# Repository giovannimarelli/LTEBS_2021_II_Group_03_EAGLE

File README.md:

# LTEBS_2021_II_Group_03_EAGLE
Laboratorio di Tecnologie Elettroniche e Biosensori S2021-II Group 03 EAGLE

In the Library folder, inside the Group_03_Library file we have inserted the two additional devices we were required to make and the microcontroller, for which we modified the footprint (setting line width of the silkscreen according to the manufacturer's specs); other devices referred to Sparkfun Library were not included, supposing to be in your possess. 
For what regards the TMUX device, we built the UQFN package, as specified by the description table inside the PDF, even if inside the provided schematic pins followed the 
TSSOP pattern. The same applies for the CY8CKIT059-TARGET: the table said to pick this, whereas inside the schematic the one used was the CY8CKIT059-TARGET_3: as before, we 
followed the table specs.

Inside the .brd file, Power Jack device looks like it exits the pcb: we intentionally placed it there folowing some examples online. 

All traces are of 10 mils, as you asked in the assignment document. However, due to the small dimension of the MUX, the design rules generated errors due to the clearance of the traces connecting the pads to the other pins. To overcome this problem, we decided to convert the width of all the traces connected to the MUX to 8 mils.

We added Silkscreen references for all SMD components, respecting manufacturer's rules of clearance and distance from the pads (8 mil from any exposed copper part).

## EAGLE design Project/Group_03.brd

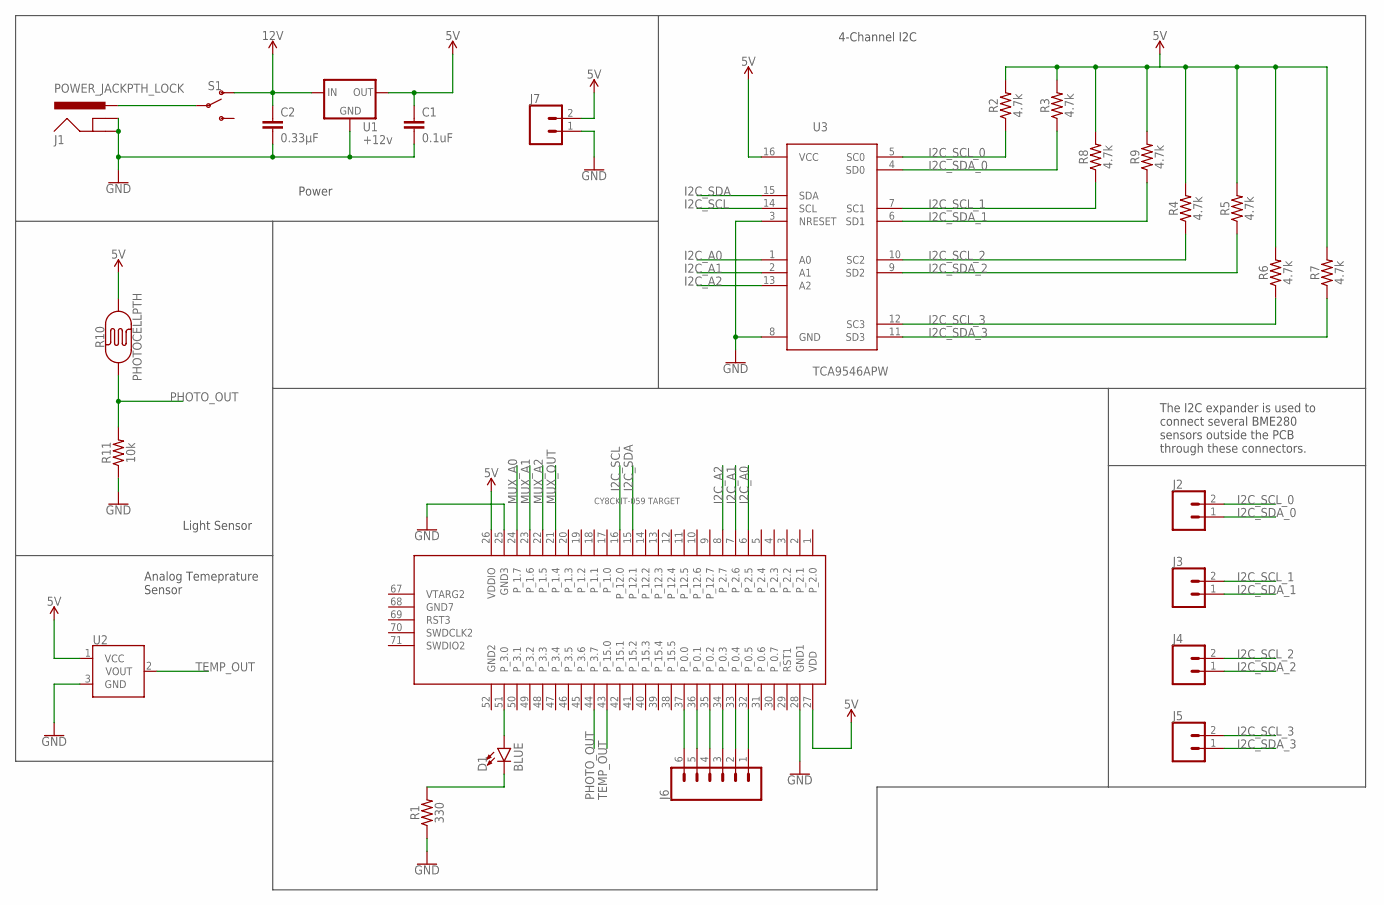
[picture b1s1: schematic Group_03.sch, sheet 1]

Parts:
C1: 0.1uF; CAP-PTH-SMALL-KIT
C2: 0.33µF; 0805
D1: BLUE; LED-1206
J1: POWER_JACKPTH_LOCK; POWER_JACK_PTH_LOCK
J2, J3, J4, J5, J7: CONN_02; 1X02
J6: CONN_06LOCK; 1X06_LOCK
R1: 330; AXIAL-0.3
R2, R3, R4, R5, R6, R7, R8, R9: 4.7k; 0603
R10: PHOTOCELLPTH; PHOTOCELL
R11: 10k; 0603
S1: SWITCH-SPDT-PTH-11.6X4.0MM; SWITCH_SPDT_PTH_11.6X4.0MM
U1: +12v; TO-252
U2: TMP36GT9; TO-92
U3: TCA9546APW; TSSOP16
U$1: CY8CKIT-059_TARGET

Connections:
5V: C1.1, J7.2, R2.2, R3.2, R4.2, R5.2, R6.2, R7.2, R8.2, R9.2, R10.2, U1.2 (OUT), U2.1 (VCC), U3.16 (VCC), U$1.26 (VDDIO), U$1.27 (VDD); also elsewhere on the board
12V: C2.1, S1.1 (O), U1.1 (IN)
GND: C1.2, C2.2, J1.GND, J1.GNDBREAK, J7.1, R1.P$1 (1), R11.1, U1.3 (GND), U2.3 (GND), U3.3 (NRESET), U3.8 (GND), U$1.25 (GND3), U$1.28 (GND1); also elsewhere on the board
I2C_A0: U3.1 (A0), U$1.6 (P_2.5)
I2C_A1: U3.2 (A1), U$1.7 (P_2.6)
I2C_A2: U3.13 (A2), U$1.8 (P_2.7)
I2C_SCL: U3.14 (SCL), U$1.16 (P_12.0)
I2C_SCL_0: J2.2, R2.1, U3.5 (SC0)
I2C_SCL_1: J3.2, R8.1, U3.7 (SC1)
I2C_SCL_2: J4.2, R4.1, U3.10 (SC2)
I2C_SCL_3: J5.2, R6.1, U3.12 (SC3)
I2C_SDA: U3.15 (SDA), U$1.15 (P_12.1)
I2C_SDA_0: J2.1, R3.1, U3.4 (SD0)
I2C_SDA_1: J3.1, R9.1, U3.6 (SD1)
I2C_SDA_2: J4.1, R5.1, U3.9 (SD2)
I2C_SDA_3: J5.1, R7.1, U3.11 (SD3)
MUX_A0: U$1.24 (P_1.7); also elsewhere on the board
MUX_A1: U$1.23 (P_1.6); also elsewhere on the board
MUX_A2: U$1.22 (P_1.5); also elsewhere on the board
MUX_OUT: U$1.21 (P_1.4); also elsewhere on the board
unnamed: J1.PWR, S1.2
unnamed: J6.1, U$1.32 (P_0.5)
unnamed: J6.2, U$1.33 (P_0.4)
unnamed: J6.3, U$1.34 (P_0.3)
unnamed: J6.4, U$1.35 (P_0.2)
unnamed: J6.5, U$1.36 (P_0.1)
unnamed: J6.6, U$1.37 (P_0.0)
unnamed: D1.A, U$1.51 (P_3.0)
unnamed: D1.C, R1.P$2 (2)
PHOTO_OUT: R10.1, R11.2, U$1.44 (P_3.7)
TEMP_OUT: U2.2 (VOUT), U$1.43 (P_15.0)

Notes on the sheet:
The I2C expander is used to connect several BME280 sensors outside the PCB through these connectors.
Analog Temeprature Sensor
Light Sensor
Power
4-Channel I2C

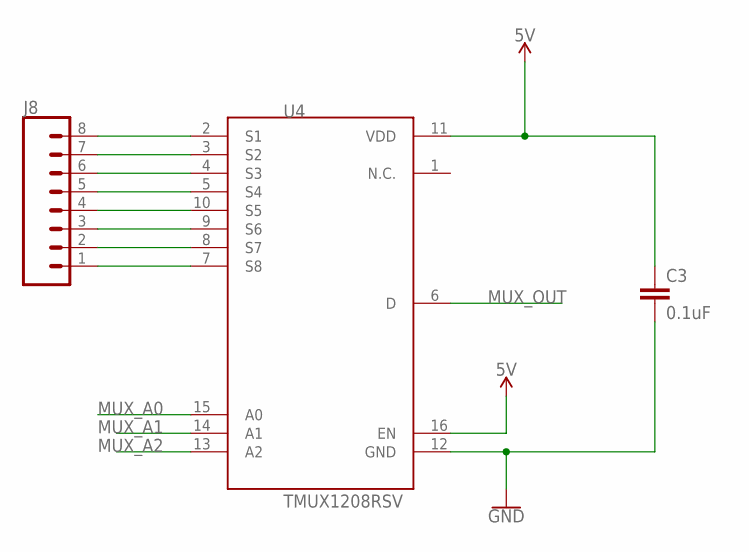
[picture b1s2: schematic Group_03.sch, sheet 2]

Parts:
C3: 0.1uF; CAP-PTH-SMALL-KIT
J8: CONN_08LOCK; 1X08_LOCK
U4: TMUX1208RSV; QFN16

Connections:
5V: C3.1, U4.11 (VDD), U4.16 (EN); also elsewhere on the board
GND: C3.2, U4.12 (GND); also elsewhere on the board
MUX_A0: U4.15 (A0); also elsewhere on the board
MUX_A1: U4.14 (A1); also elsewhere on the board
MUX_A2: U4.13 (A2); also elsewhere on the board
MUX_OUT: U4.6 (D); also elsewhere on the board
unnamed: J8.8, U4.2 (S1)
unnamed: J8.7, U4.3 (S2)
unnamed: J8.6, U4.4 (S3)
unnamed: J8.5, U4.5 (S4)
unnamed: J8.4, U4.10 (S5)
unnamed: J8.3, U4.9 (S6)
unnamed: J8.2, U4.8 (S7)
unnamed: J8.1, U4.7 (S8)

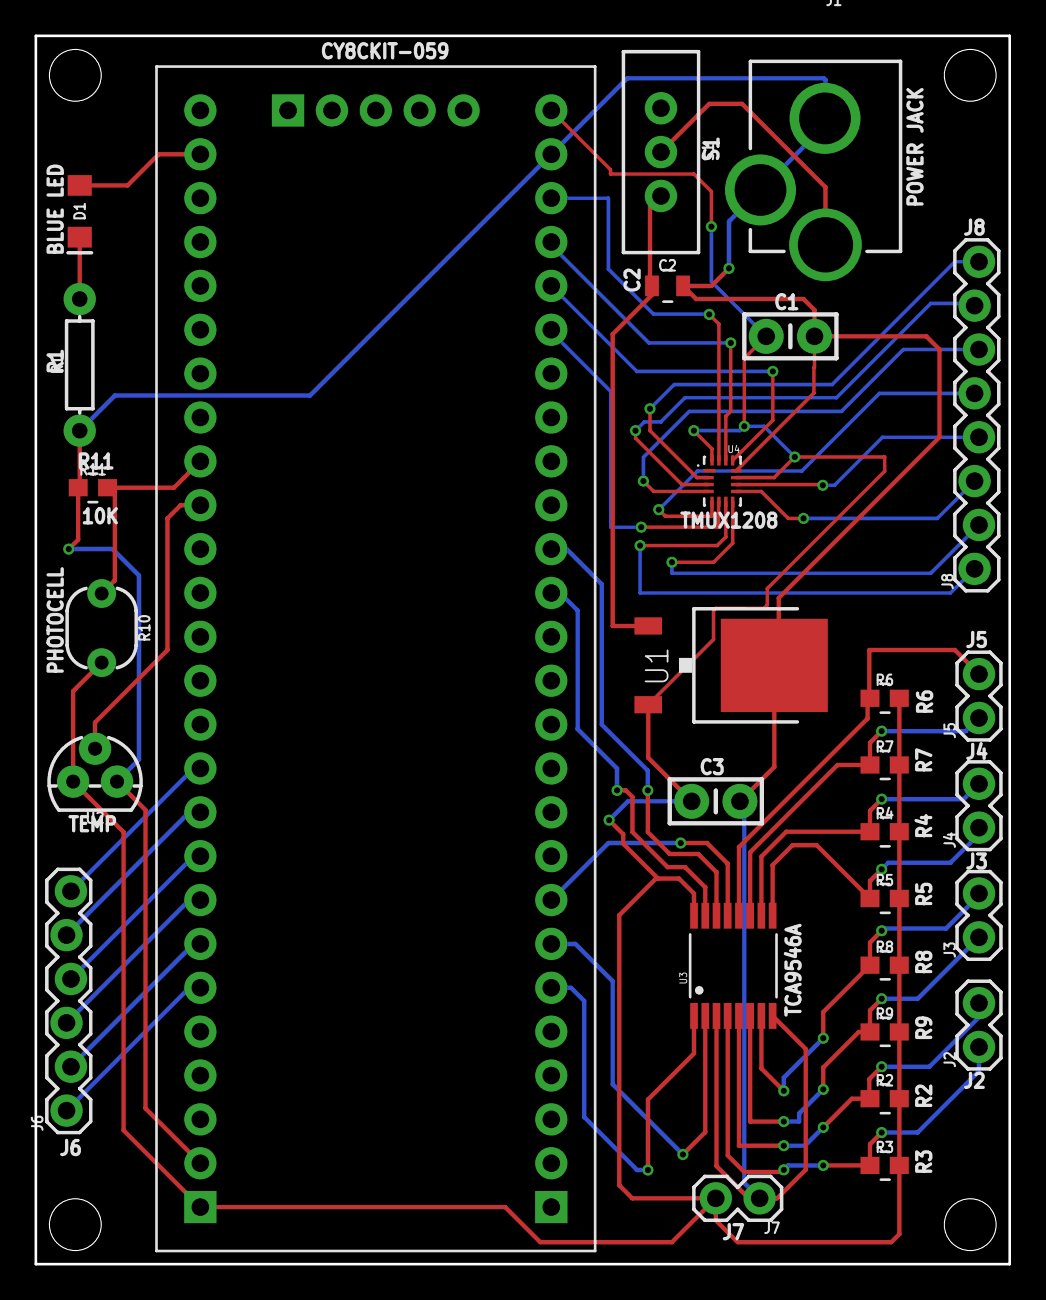
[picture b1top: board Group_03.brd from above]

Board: 2 copper layers, 56.4 x 71.1 mm, 29 parts (0 on the bottom side), 39 nets.

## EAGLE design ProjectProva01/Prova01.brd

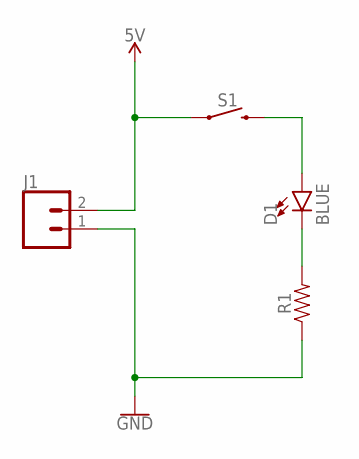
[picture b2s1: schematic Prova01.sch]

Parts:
D1: BLUE; LED-0603
J1: CONN_02; 1X02
R1: AXIAL-0.3
S1: MOMENTARY-SWITCH-SPST-PTH-6.0MM; TACTILE_SWITCH_PTH_6.0MM

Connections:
5V: J1.2, S1.1
GND: J1.1, R1.P$1 (1)
unnamed: D1.A, S1.3 (2)
unnamed: D1.C, R1.P$2 (2)

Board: 2 copper layers, 4 parts (0 on the bottom side), 4 nets, no tracks yet.

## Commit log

2021-03-18 Add .gitignore file
2021-03-18 Removed pdf
2021-03-18 Removed files
2021-03-18 Epf modification
2021-03-18 Remove folder
2021-03-18 Re-add folder to apply .gitignore
2021-03-18 Folder con schematico di prova
2021-03-18 Aggiunta del file PCB (.brd)
2021-03-18 Immagine a caso
2021-03-18 Elimino immagine
2021-03-19 Add Design Rules folder
2021-03-19 Remove folder di prova
2021-03-19 Add TMUX1208 to the Library
2021-03-19 Correction of pin/pad connection
2021-03-19 Add TCA9546A to library
2021-03-19 Start of the schematic, PowerJack, Conn2
2021-03-19 Add light and temperature sensors
2021-03-19 Layout editing
2021-03-20 Add 4-Channel I2C
2021-03-20 Add last comments + layout editing
2021-03-20 Add of TMUX and CY8CKIT
2021-03-20 Generation of empty board
2021-03-20 Geenration of first version of design rules
2021-03-20 Start of PCB placing
2021-03-20 Placement on board completed
2021-03-20 Move names
2021-03-20 Moved CY8CKIT
2021-03-20 First board layout attempt
2021-03-20 Parts placement (size 73.66x71.12)
2021-03-20 Blue vias version (71.12x60.96)
2021-03-21 Completed wiring, and design rules update
2021-03-21 Silkscreen names
2021-03-21 Copper pour both layers
2021-03-22 Clearance errors fixed
2021-03-22 Change silkscreen line width in Library for MUX, TCA and CY8
2021-03-22 Last modifications to schematic, board and check rules
2021-03-26 Silscreen SMD components
2021-03-26 Silkscreen adjustment for custom components
2021-03-26 Polygon isolation correction
2021-03-26 Last modifications
2021-03-26 Final update of README
2021-03-26 Final version

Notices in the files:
parts and their libraries:
SparkFun-Capacitors: Licensing: Creative Commons ShareAlike 4.0 International - https://creativecommons.org/licenses/by-sa/4.0
